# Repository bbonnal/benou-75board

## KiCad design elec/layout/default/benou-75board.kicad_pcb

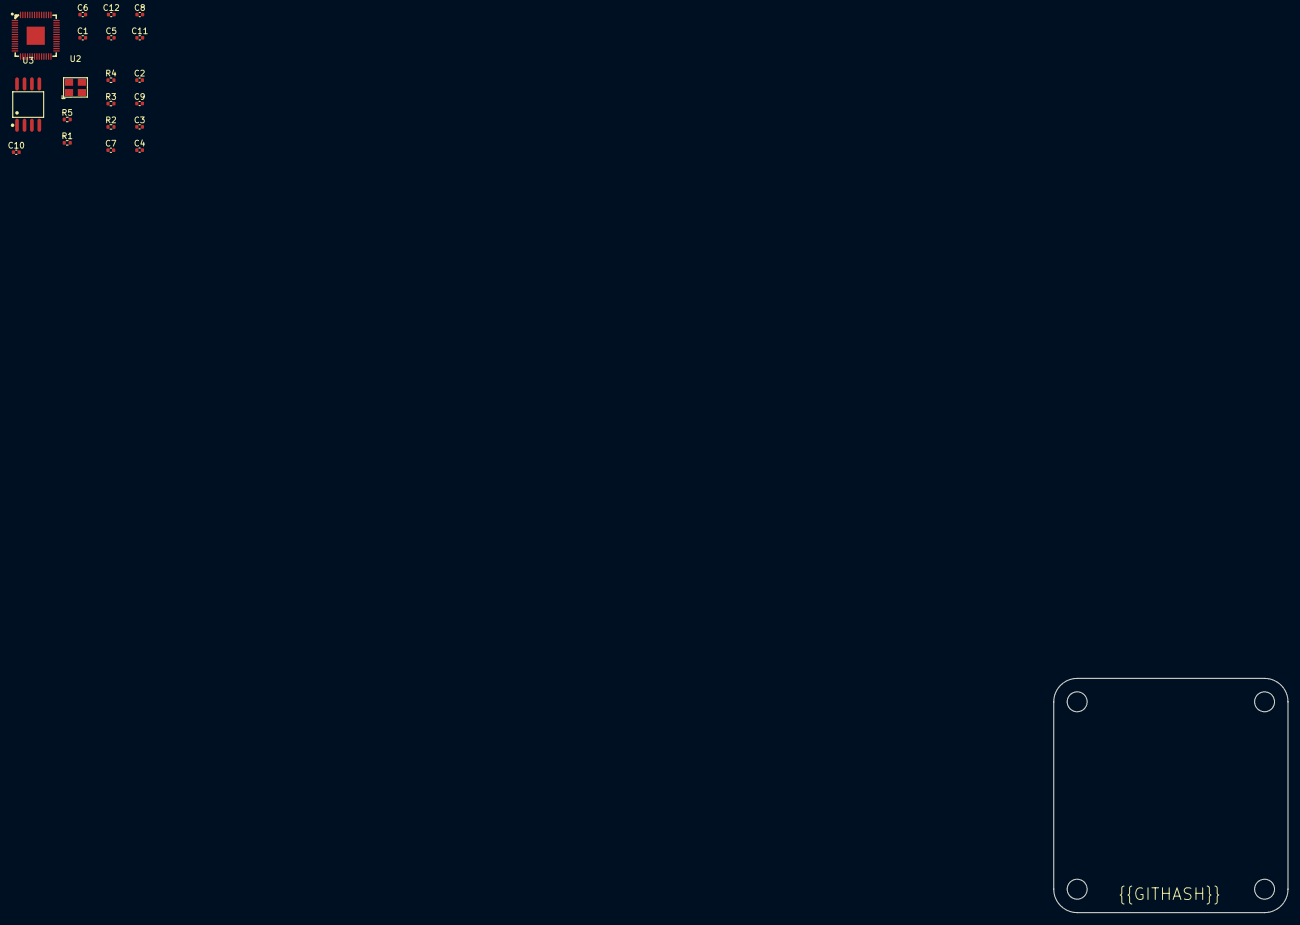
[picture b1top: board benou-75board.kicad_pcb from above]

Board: 2 copper layers, 40.0 x 40.0 mm, 20 parts (0 on the bottom side), 15 nets, no tracks yet.

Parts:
C1, C2: 22.0 pF; C0402
C3, C4, C5, C6, C7, C9, C10, C11: 100.0 nF; C0402
C8, C12: 1.0 uF; C0402
R1: 1.0 KΩ; R0402
R2, R3: 27.0 KΩ; R0402
R4, R5: 10.0 KΩ; R0402
U1: LQFN-56_L7.0-W7.0-P0.4-EP
U2: OSC-SMD_4P-L3.2-W2.5-BL
U3: SOIC-8_L5.3-W5.3-P1.27-LS8.0-BL

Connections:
cs: R5.2, U1.56, U3.1
gnd: C1.2, C2.2, C3.2, C4.2, C5.2, C6.2, C7.2, C8.2, C9.2, C10.2, C11.2, C12.2, U1.19, U1.57, U2.2, U2.4, U3.4
io0: U1.53, U3.5
io1: U1.55, U3.2
io2: U1.54, U3.3
io3: U1.51, U3.7
run: R4.2, U1.26
sck: U1.52, U3.6
usb_dm: R3.2, U1.46
usb_dp: R2.1, U1.47
vcc: C3.1, C4.1, C5.1, C6.1, C7.1, C8.1, R4.1, R5.1, U1.1, U1.10, U1.22, U1.33, U1.42, U1.43, U1.44, U1.48, U1.49, U3.8
vcc-1: C9.1, C10.1, C11.1, C12.1, U1.23, U1.45, U1.50
vcc-2: C1.1, U1.20, U2.1
vcc-3: C2.1, R1.2, U2.3
xout: R1.1, U1.21

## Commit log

2024-01-19 Initial import
2024-01-19 Initial RP2040 kit
